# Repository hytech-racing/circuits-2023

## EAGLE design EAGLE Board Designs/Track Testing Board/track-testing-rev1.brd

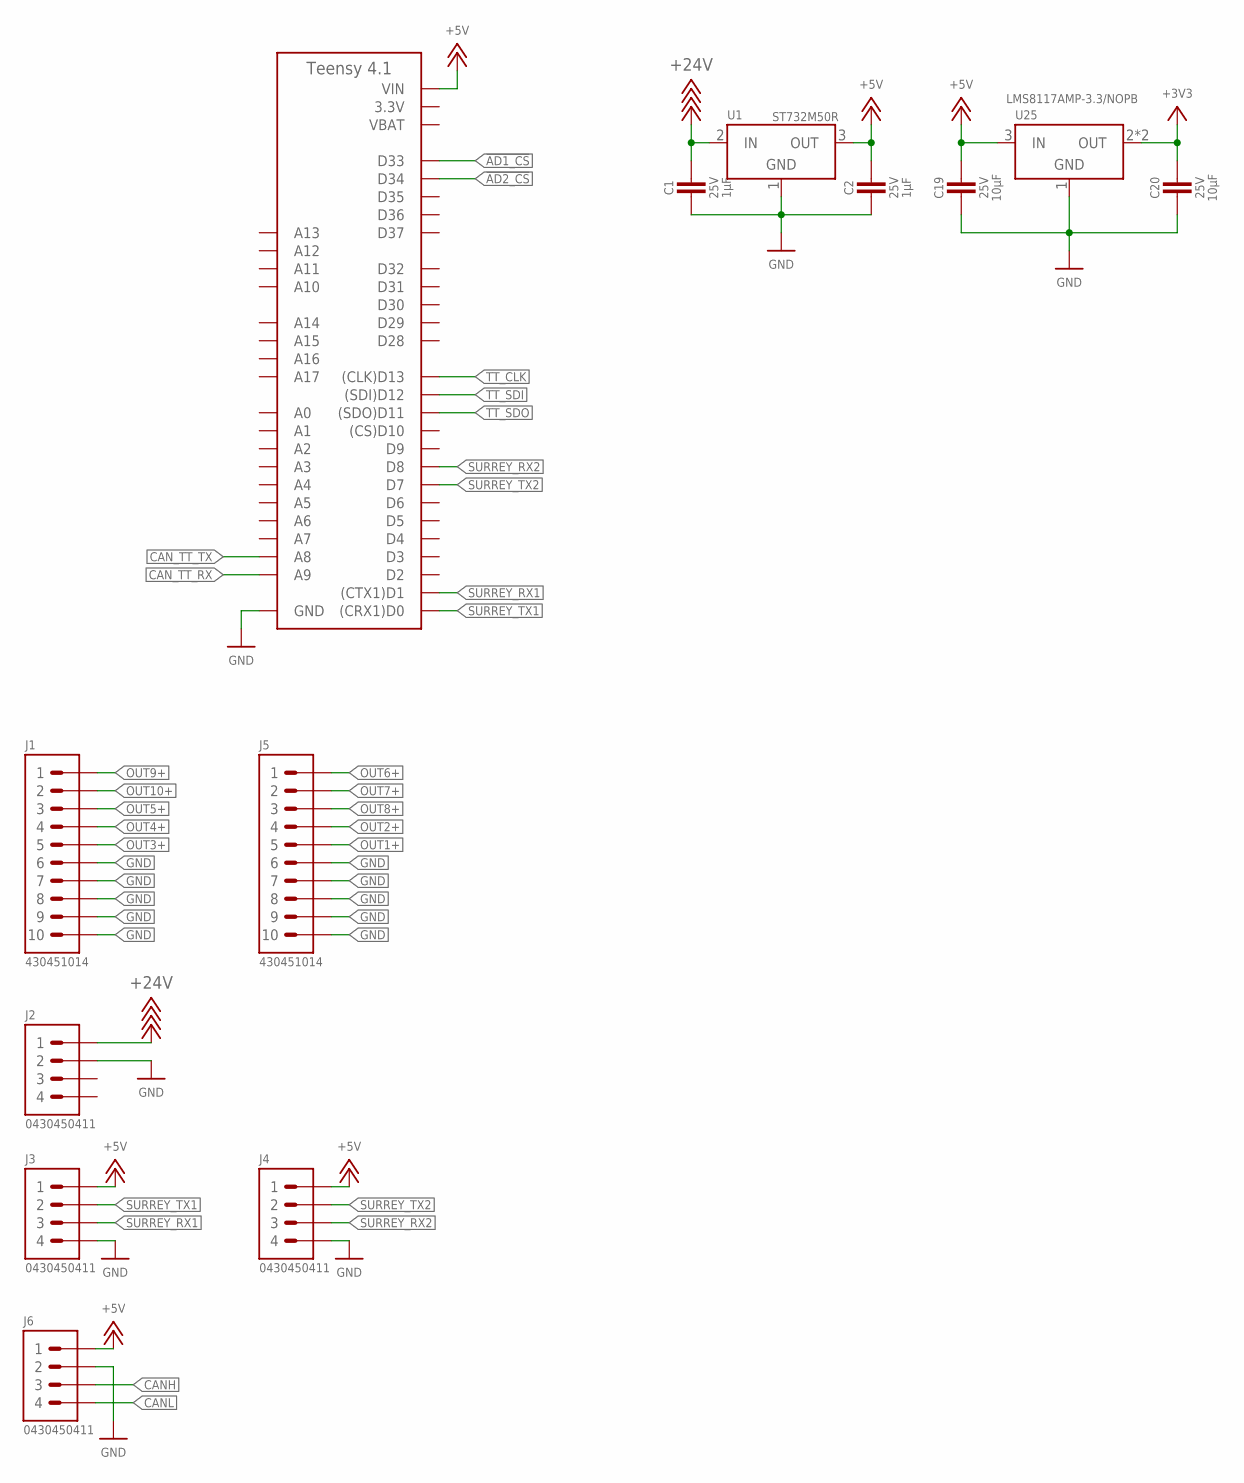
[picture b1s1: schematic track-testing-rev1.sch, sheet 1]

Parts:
A1: TEENSY_4.1; TEENSY_LONG_EXT
C1, C2: CAPACITOR_0603_25V_1UF; 0603-CAP
C19, C20: CAPACITOR_0603_25V_10UF; 0603-CAP
J1, J5: CONNECTOR-10_MF_T_V_; MOLEX_MICROFIT_PTH_VERTICAL_10_DUAL
J2, J3, J4, J6: CONNECTOR-4_μF_S_RA_; MOLEX_MICROFIT_SMD_RIGHTANGLE_04_DUAL
U1: VOLTAGE_REGULATOR_SOT-23-5_5V; SOT-23-5
U25: VOLTAGE_REGULATOR_SOT-223_3.3V; SOT-223

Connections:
3.3V: A1.3V3 (3.3V), A1.3V3@2 (3.3V), A1.3V3@3 (3.3V)
!AD1_CS: A1.D33; also elsewhere on the board
!AD2_CS: A1.D34; also elsewhere on the board
+3V3: C20.1, U25.2 (OUT), U25.4 (OUT); also elsewhere on the board
+5V: A1.VIN, C2.1, C19.1, J3.1, J4.1, J6.1, U1.3 (OUT), U25.3 (IN); also elsewhere on the board
+24V: C1.1, J2.1, U1.2 (IN)
CANH: J6.3; also elsewhere on the board
CANL: J6.4; also elsewhere on the board
CAN_TT_RX: A1.D23 (A9); also elsewhere on the board
CAN_TT_TX: A1.D22 (A8); also elsewhere on the board
GND: A1.AGND/GND (GND), A1.GND, A1.GND@2 (GND), C1.2, C2.2, C19.2, C20.2, J1.6, J1.7, J1.8, J1.9, J1.10, J2.2, J3.4, J4.4, J5.6, J5.7, J5.8, J5.9, J5.10, J6.2, U1.1 (GND), U25.1 (GND); also elsewhere on the board
OUT1+: J5.5; also elsewhere on the board
OUT2+: J5.4; also elsewhere on the board
OUT3+: J1.5; also elsewhere on the board
OUT4+: J1.4; also elsewhere on the board
OUT5+: J1.3; also elsewhere on the board
OUT6+: J5.1; also elsewhere on the board
OUT7+: J5.2; also elsewhere on the board
OUT8+: J5.3; also elsewhere on the board
OUT9+: J1.1; also elsewhere on the board
OUT10+: J1.2; also elsewhere on the board
SURREY_RX1: A1.D1 ((CTX1)D1), J3.3
SURREY_RX2: A1.D8, J4.3
SURREY_TX1: A1.D0 ((CRX1)D0), J3.2
SURREY_TX2: A1.D7, J4.2
TT_CLK: A1.D13 ((CLK)D13); also elsewhere on the board
TT_SDI: A1.D12 ((SDI)D12); also elsewhere on the board
TT_SDO: A1.D11 ((SDO)D11); also elsewhere on the board
VBAT: A1.VBAT

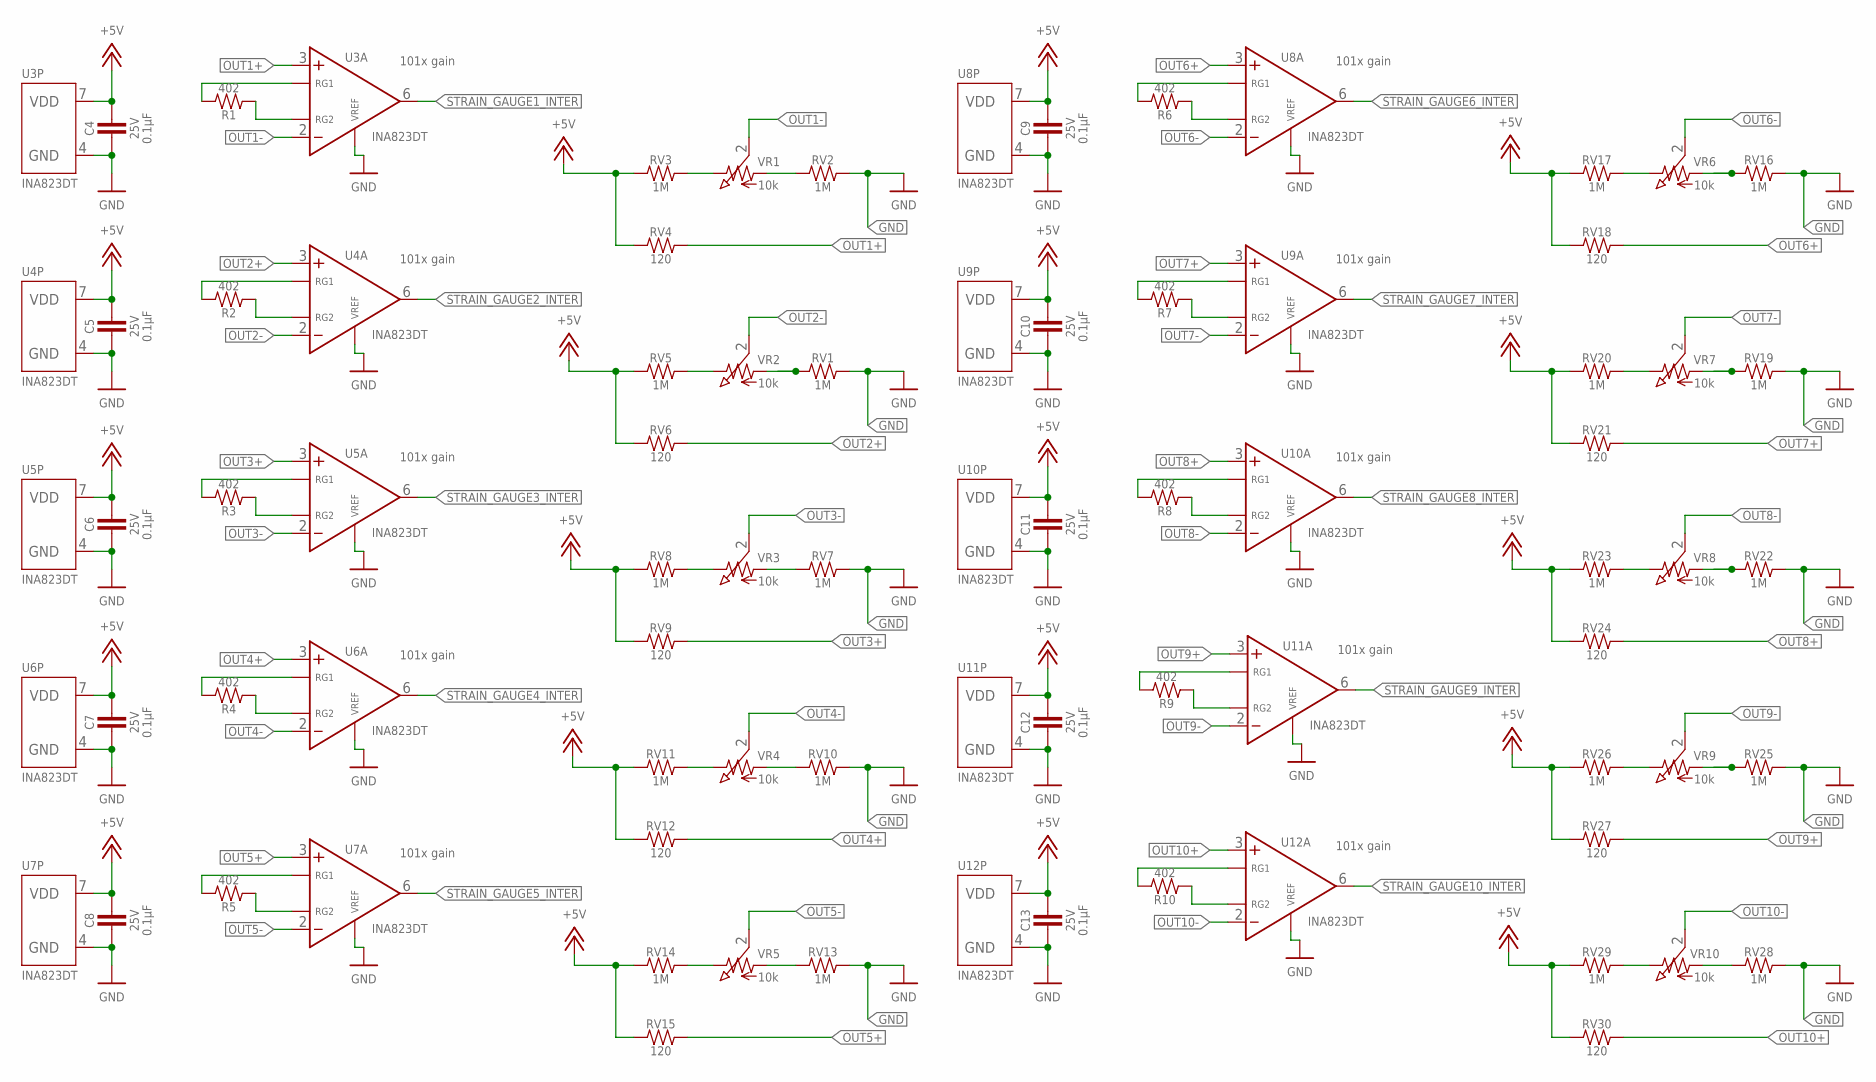
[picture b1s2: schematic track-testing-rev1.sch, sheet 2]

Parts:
C4, C5, C6, C7, C8, C9, C10, C11, C12, C13: CAPACITOR_0603_25V_0.1UF; 0603-CAP
R1, R2, R3, R4, R5, R6, R7, R8, R9, R10: RESISTOR_0603_402; 0603-RES
RV1, RV2, RV3, RV5, RV7, RV8, RV10, RV11, RV13, RV14, RV16, RV17, RV19, RV20, RV22, RV23, RV25, RV26, RV28, RV29: 1M; 0603-RES
RV4, RV6, RV9, RV12, RV15, RV18, RV21, RV24, RV27, RV30: 120; 0603-RES
U3, U4, U5, U6, U7, U8, U9, U10, U11, U12: INA823DT; SOIC-08(NARROW,0.15")
VR1, VR2, VR3, VR4, VR5, VR6, VR7, VR8, VR9, VR10: RESISTOR_TRIMPOT_10K_3362P; 3362P

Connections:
+5V: C4.1, C5.1, C6.1, C7.1, C8.1, C9.1, C10.1, C11.1, C12.1, C13.1, RV3.1, RV4.1, RV5.1, RV6.1, RV8.1, RV9.1, RV11.1, RV12.1, RV14.1, RV15.1, RV17.1, RV18.1, RV20.1, RV21.1, RV23.1, RV24.1, RV26.1, RV27.1, RV29.1, RV30.1, U3.7 (VDD), U4.7 (VDD), U5.7 (VDD), U6.7 (VDD), U7.7 (VDD), U8.7 (VDD), U9.7 (VDD), U10.7 (VDD), U11.7 (VDD), U12.7 (VDD); also elsewhere on the board
GND: C4.2, C5.2, C6.2, C7.2, C8.2, C9.2, C10.2, C11.2, C12.2, C13.2, RV1.2, RV2.2, RV7.2, RV10.2, RV13.2, RV16.2, RV19.2, RV22.2, RV25.2, RV28.2, U3.4 (GND), U3.5 (VREF), U4.4 (GND), U4.5 (VREF), U5.4 (GND), U5.5 (VREF), U6.4 (GND), U6.5 (VREF), U7.4 (GND), U7.5 (VREF), U8.4 (GND), U8.5 (VREF), U9.4 (GND), U9.5 (VREF), U10.4 (GND), U10.5 (VREF), U11.4 (GND), U11.5 (VREF), U12.4 (GND), U12.5 (VREF); also elsewhere on the board
unnamed: R2.2, U4.1 (RG1)
unnamed: R1.2, U3.1 (RG1)
unnamed: R1.1, U3.8 (RG2)
unnamed: R2.1, U4.8 (RG2)
unnamed: R3.2, U5.1 (RG1)
unnamed: R6.2, U8.1 (RG1)
unnamed: R3.1, U5.8 (RG2)
unnamed: R6.1, U8.8 (RG2)
unnamed: R4.2, U6.1 (RG1)
unnamed: R7.2, U9.1 (RG1)
unnamed: R4.1, U6.8 (RG2)
unnamed: R5.2, U7.1 (RG1)
unnamed: R5.1, U7.8 (RG2)
unnamed: R7.1, U9.8 (RG2)
unnamed: R8.2, U10.1 (RG1)
unnamed: R8.1, U10.8 (RG2)
unnamed: R9.2, U11.1 (RG1)
unnamed: R9.1, U11.8 (RG2)
unnamed: R10.2, U12.1 (RG1)
unnamed: R10.1, U12.8 (RG2)
unnamed: RV2.1, VR1.1
unnamed: RV3.2, VR1.3 (2)
unnamed: RV1.1, VR2.1
unnamed: RV5.2, VR2.3 (2)
unnamed: RV11.2, VR4.3 (2)
unnamed: RV7.1, VR3.1
unnamed: RV8.2, VR3.3 (2)
unnamed: RV10.1, VR4.1
unnamed: RV14.2, VR5.3 (2)
unnamed: RV13.1, VR5.1
unnamed: RV16.1, VR6.1
unnamed: RV17.2, VR6.3 (2)
unnamed: RV19.1, VR7.1
unnamed: RV20.2, VR7.3 (2)
unnamed: RV22.1, VR8.1
unnamed: RV23.2, VR8.3 (2)
unnamed: RV25.1, VR9.1
unnamed: RV26.2, VR9.3 (2)
unnamed: RV28.1, VR10.1
unnamed: RV29.2, VR10.3 (2)
OUT1+: RV4.2, U3.3 (VIN+); also elsewhere on the board
OUT1-: U3.2 (VIN-), VR1.2 (3)
OUT2+: RV6.2, U4.3 (VIN+); also elsewhere on the board
OUT2-: U4.2 (VIN-), VR2.2 (3)
OUT3+: RV9.2, U5.3 (VIN+); also elsewhere on the board
OUT3-: U5.2 (VIN-), VR3.2 (3)
OUT4+: RV12.2, U6.3 (VIN+); also elsewhere on the board
OUT4-: U6.2 (VIN-), VR4.2 (3)
OUT5+: RV15.2, U7.3 (VIN+); also elsewhere on the board
OUT5-: U7.2 (VIN-), VR5.2 (3)
OUT6+: RV18.2, U8.3 (VIN+); also elsewhere on the board
OUT6-: U8.2 (VIN-), VR6.2 (3)
OUT7+: RV21.2, U9.3 (VIN+); also elsewhere on the board
OUT7-: U9.2 (VIN-), VR7.2 (3)
OUT8+: RV24.2, U10.3 (VIN+); also elsewhere on the board
OUT8-: U10.2 (VIN-), VR8.2 (3)
OUT9+: RV27.2, U11.3 (VIN+); also elsewhere on the board
OUT9-: U11.2 (VIN-), VR9.2 (3)
OUT10+: RV30.2, U12.3 (VIN+); also elsewhere on the board
OUT10-: U12.2 (VIN-), VR10.2 (3)
STRAIN_GAUGE1_INTER: U3.6 (VOUT); also elsewhere on the board
STRAIN_GAUGE2_INTER: U4.6 (VOUT); also elsewhere on the board
STRAIN_GAUGE3_INTER: U5.6 (VOUT); also elsewhere on the board
STRAIN_GAUGE4_INTER: U6.6 (VOUT); also elsewhere on the board
STRAIN_GAUGE5_INTER: U7.6 (VOUT); also elsewhere on the board
STRAIN_GAUGE6_INTER: U8.6 (VOUT); also elsewhere on the board
STRAIN_GAUGE7_INTER: U9.6 (VOUT); also elsewhere on the board
STRAIN_GAUGE8_INTER: U10.6 (VOUT); also elsewhere on the board
STRAIN_GAUGE9_INTER: U11.6 (VOUT); also elsewhere on the board
STRAIN_GAUGE10_INTER: U12.6 (VOUT); also elsewhere on the board

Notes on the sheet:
101x gain

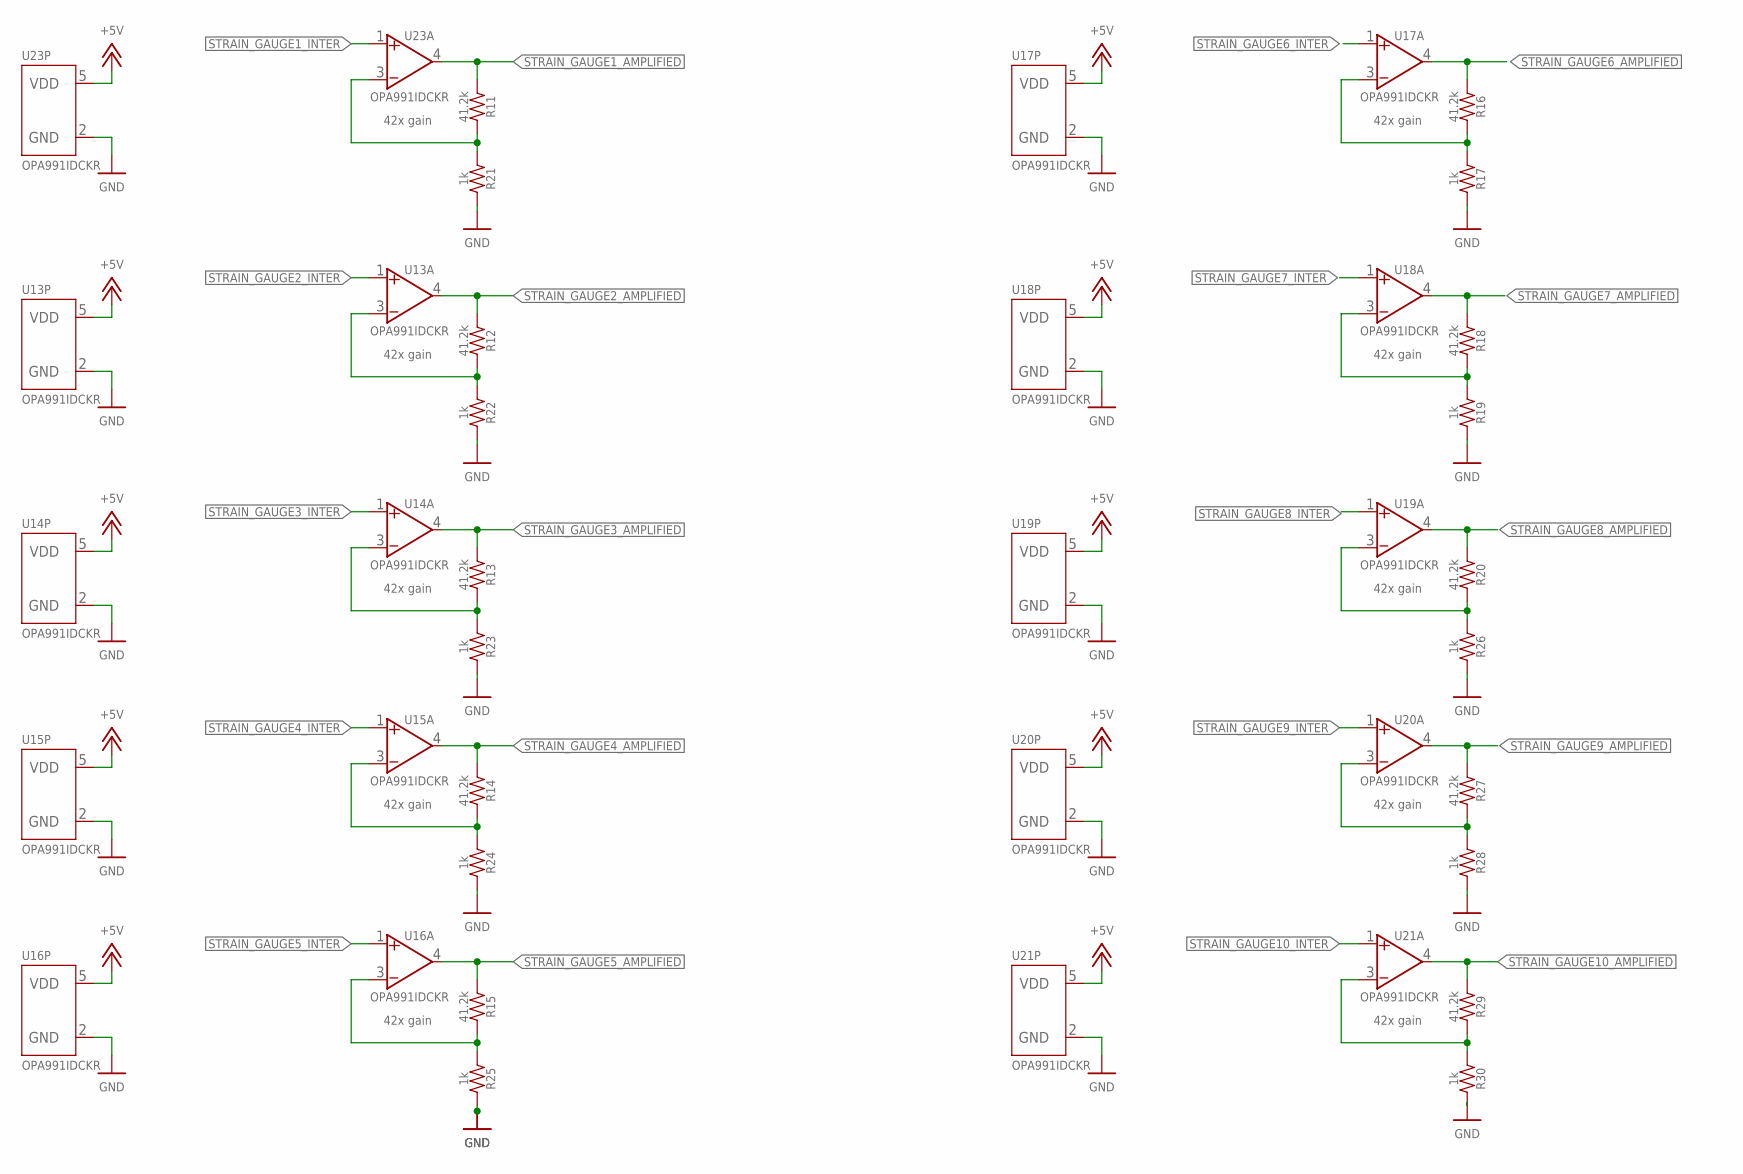
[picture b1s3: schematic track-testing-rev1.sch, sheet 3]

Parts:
R11, R12, R13, R14, R15, R16, R18, R20, R27, R29: RESISTOR_0603_41.2K; 0603-RES
R17, R19, R21, R22, R23, R24, R25, R26, R28, R30: RESISTOR_0603_1K; 0603-RES
U13, U14, U15, U16, U17, U18, U19, U20, U21, U23: OPAMP_1_CHANNEL_OPA991; SC-70-5

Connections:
+5V: U13.5 (VDD), U14.5 (VDD), U15.5 (VDD), U16.5 (VDD), U17.5 (VDD), U18.5 (VDD), U19.5 (VDD), U20.5 (VDD), U21.5 (VDD), U23.5 (VDD); also elsewhere on the board
GND: R17.2, R19.2, R21.2, R22.2, R23.2, R24.2, R25.2, R26.2, R28.2, R30.2, U13.2 (GND), U14.2 (GND), U15.2 (GND), U16.2 (GND), U17.2 (GND), U18.2 (GND), U19.2 (GND), U20.2 (GND), U21.2 (GND), U23.2 (GND); also elsewhere on the board
unnamed: R12.2, R22.1, U13.3 (VIN-)
unnamed: R11.2, R21.1, U23.3 (VIN-)
unnamed: R13.2, R23.1, U14.3 (VIN-)
unnamed: R14.2, R24.1, U15.3 (VIN-)
unnamed: R15.2, R25.1, U16.3 (VIN-)
unnamed: R16.2, R17.1, U17.3 (VIN-)
unnamed: R18.2, R19.1, U18.3 (VIN-)
unnamed: R20.2, R26.1, U19.3 (VIN-)
unnamed: R27.2, R28.1, U20.3 (VIN-)
unnamed: R29.2, R30.1, U21.3 (VIN-)
STRAIN_GAUGE1_AMPLIFIED: R11.1, U23.4 (VOUT); also elsewhere on the board
STRAIN_GAUGE1_INTER: U23.1 (VIN+); also elsewhere on the board
STRAIN_GAUGE2_AMPLIFIED: R12.1, U13.4 (VOUT); also elsewhere on the board
STRAIN_GAUGE2_INTER: U13.1 (VIN+); also elsewhere on the board
STRAIN_GAUGE3_AMPLIFIED: R13.1, U14.4 (VOUT); also elsewhere on the board
STRAIN_GAUGE3_INTER: U14.1 (VIN+); also elsewhere on the board
STRAIN_GAUGE4_AMPLIFIED: R14.1, U15.4 (VOUT); also elsewhere on the board
STRAIN_GAUGE4_INTER: U15.1 (VIN+); also elsewhere on the board
STRAIN_GAUGE5_AMPLIFIED: R15.1, U16.4 (VOUT); also elsewhere on the board
STRAIN_GAUGE5_INTER: U16.1 (VIN+); also elsewhere on the board
STRAIN_GAUGE6_AMPLIFIED: R16.1, U17.4 (VOUT); also elsewhere on the board
STRAIN_GAUGE6_INTER: U17.1 (VIN+); also elsewhere on the board
STRAIN_GAUGE7_AMPLIFIED: R18.1, U18.4 (VOUT); also elsewhere on the board
STRAIN_GAUGE7_INTER: U18.1 (VIN+); also elsewhere on the board
STRAIN_GAUGE8_AMPLIFIED: R20.1, U19.4 (VOUT); also elsewhere on the board
STRAIN_GAUGE8_INTER: U19.1 (VIN+); also elsewhere on the board
STRAIN_GAUGE9_AMPLIFIED: R27.1, U20.4 (VOUT); also elsewhere on the board
STRAIN_GAUGE9_INTER: U20.1 (VIN+); also elsewhere on the board
STRAIN_GAUGE10_AMPLIFIED: R29.1, U21.4 (VOUT); also elsewhere on the board
STRAIN_GAUGE10_INTER: U21.1 (VIN+); also elsewhere on the board

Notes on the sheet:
42x gain

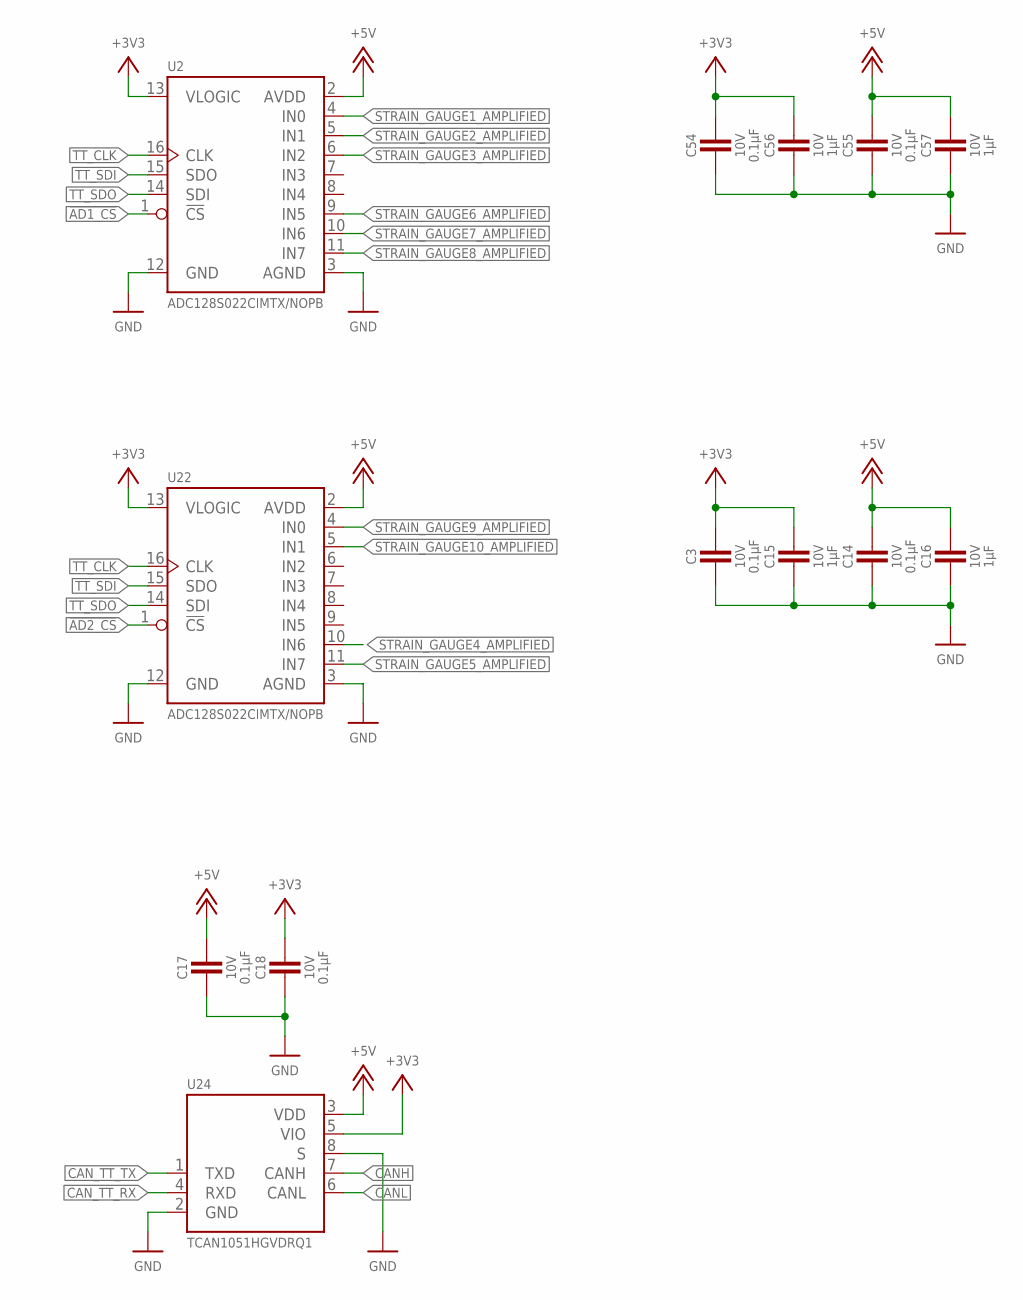
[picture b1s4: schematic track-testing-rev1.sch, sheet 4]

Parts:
C3, C14, C17, C18, C54, C55: CAPACITOR_0603_10V_0.1UF; 0603-CAP
C15, C16, C56, C57: CAPACITOR_0603_10V_1UF; 0603-CAP
U2, U22: ADC128S022; TSSOP-16
U24: TCAN1051HQV-Q1; SOIC-08(NARROW,0.15")

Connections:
!AD1_CS: U2.1 (!CS!); also elsewhere on the board
!AD2_CS: U22.1 (!CS!); also elsewhere on the board
+3V3: C3.1, C15.1, C18.1, C54.1, C56.1, U2.13 (VLOGIC), U22.13 (VLOGIC), U24.5 (VIO); also elsewhere on the board
+5V: C14.1, C16.1, C17.1, C55.1, C57.1, U2.2 (AVDD), U22.2 (AVDD), U24.3 (VDD); also elsewhere on the board
CANH: U24.7 (CANH); also elsewhere on the board
CANL: U24.6 (CANL); also elsewhere on the board
CAN_TT_RX: U24.4 (RXD); also elsewhere on the board
CAN_TT_TX: U24.1 (TXD); also elsewhere on the board
GND: C3.2, C14.2, C15.2, C16.2, C17.2, C18.2, C54.2, C55.2, C56.2, C57.2, U2.3 (AGND), U2.12 (GND), U22.3 (AGND), U22.12 (GND), U24.2 (GND), U24.8 (S); also elsewhere on the board
STRAIN_GAUGE1_AMPLIFIED: U2.4 (IN0); also elsewhere on the board
STRAIN_GAUGE2_AMPLIFIED: U2.5 (IN1); also elsewhere on the board
STRAIN_GAUGE3_AMPLIFIED: U2.6 (IN2); also elsewhere on the board
STRAIN_GAUGE4_AMPLIFIED: U22.10 (IN6); also elsewhere on the board
STRAIN_GAUGE5_AMPLIFIED: U22.11 (IN7); also elsewhere on the board
STRAIN_GAUGE6_AMPLIFIED: U2.9 (IN5); also elsewhere on the board
STRAIN_GAUGE7_AMPLIFIED: U2.10 (IN6); also elsewhere on the board
STRAIN_GAUGE8_AMPLIFIED: U2.11 (IN7); also elsewhere on the board
STRAIN_GAUGE9_AMPLIFIED: U22.4 (IN0); also elsewhere on the board
STRAIN_GAUGE10_AMPLIFIED: U22.5 (IN1); also elsewhere on the board
TT_CLK: U2.16 (CLK), U22.16 (CLK); also elsewhere on the board
TT_SDI: U2.15 (SDO), U22.15 (SDO); also elsewhere on the board
TT_SDO: U2.14 (SDI), U22.14 (SDI); also elsewhere on the board

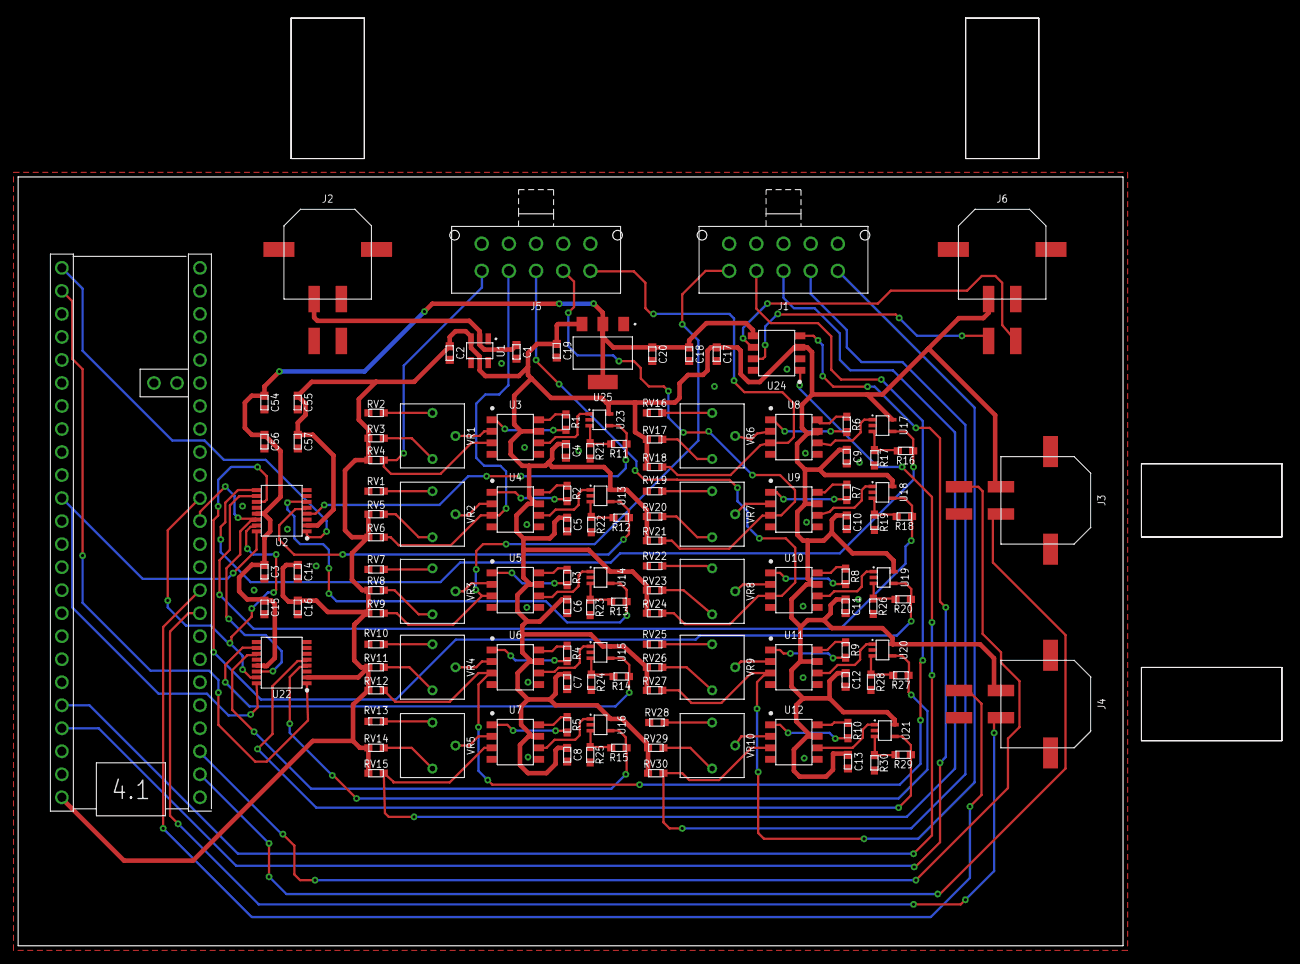
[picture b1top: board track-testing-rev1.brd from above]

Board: 2 copper layers, 139.4 x 102.4 mm, 126 parts (0 on the bottom side), 108 nets.

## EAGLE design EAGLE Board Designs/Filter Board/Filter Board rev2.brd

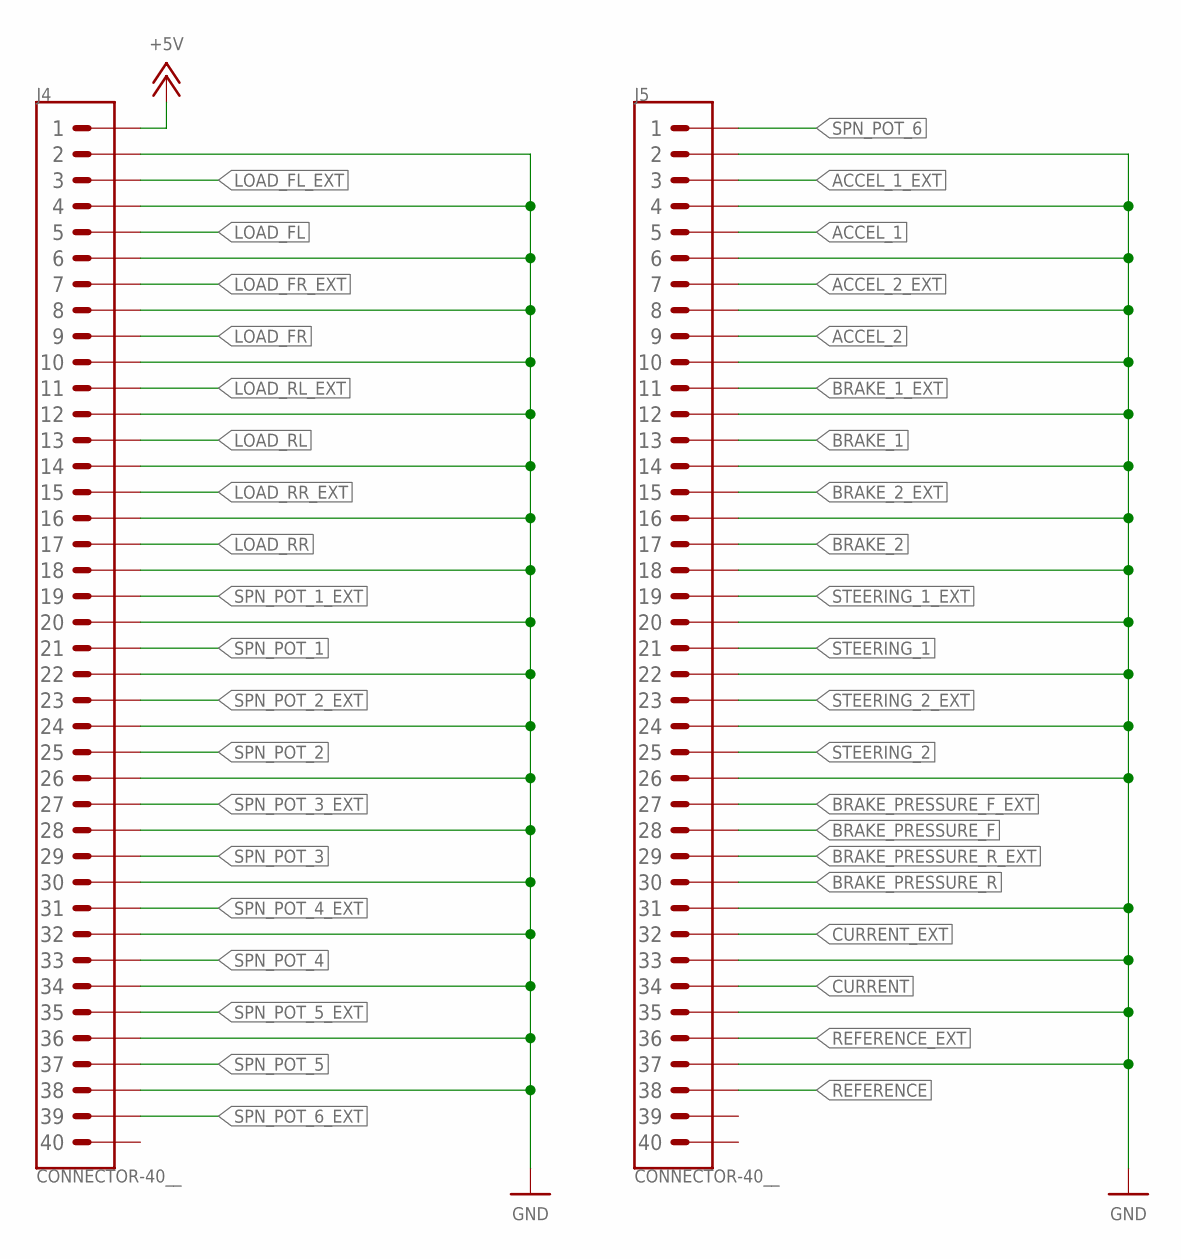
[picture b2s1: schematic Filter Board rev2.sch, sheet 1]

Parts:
J4, J5: CONNECTOR-40__; EHT-120-01

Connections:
+5V: J4.1; also elsewhere on the board
ACCEL_1: J5.5; also elsewhere on the board
ACCEL_1_EXT: J5.3; also elsewhere on the board
ACCEL_2: J5.9; also elsewhere on the board
ACCEL_2_EXT: J5.7; also elsewhere on the board
BRAKE_1: J5.13; also elsewhere on the board
BRAKE_1_EXT: J5.11; also elsewhere on the board
BRAKE_2: J5.17; also elsewhere on the board
BRAKE_2_EXT: J5.15; also elsewhere on the board
BRAKE_PRESSURE_F: J5.28; also elsewhere on the board
BRAKE_PRESSURE_F_EXT: J5.27; also elsewhere on the board
BRAKE_PRESSURE_R: J5.30; also elsewhere on the board
BRAKE_PRESSURE_R_EXT: J5.29; also elsewhere on the board
CURRENT: J5.34; also elsewhere on the board
CURRENT_EXT: J5.32; also elsewhere on the board
GND: J4.2, J4.4, J4.6, J4.8, J4.10, J4.12, J4.14, J4.16, J4.18, J4.20, J4.22, J4.24, J4.26, J4.28, J4.30, J4.32, J4.34, J4.36, J4.38, J5.2, J5.4, J5.6, J5.8, J5.10, J5.12, J5.14, J5.16, J5.18, J5.20, J5.22, J5.24, J5.26, J5.31, J5.33, J5.35, J5.37; also elsewhere on the board
LOAD_FL: J4.5; also elsewhere on the board
LOAD_FL_EXT: J4.3; also elsewhere on the board
LOAD_FR: J4.9; also elsewhere on the board
LOAD_FR_EXT: J4.7; also elsewhere on the board
LOAD_RL: J4.13; also elsewhere on the board
LOAD_RL_EXT: J4.11; also elsewhere on the board
LOAD_RR: J4.17; also elsewhere on the board
LOAD_RR_EXT: J4.15; also elsewhere on the board
REFERENCE: J5.38; also elsewhere on the board
REFERENCE_EXT: J5.36; also elsewhere on the board
SPN_POT_1: J4.21; also elsewhere on the board
SPN_POT_1_EXT: J4.19; also elsewhere on the board
SPN_POT_2: J4.25; also elsewhere on the board
SPN_POT_2_EXT: J4.23; also elsewhere on the board
SPN_POT_3: J4.29; also elsewhere on the board
SPN_POT_3_EXT: J4.27; also elsewhere on the board
SPN_POT_4: J4.33; also elsewhere on the board
SPN_POT_4_EXT: J4.31; also elsewhere on the board
SPN_POT_5: J4.37; also elsewhere on the board
SPN_POT_5_EXT: J4.35; also elsewhere on the board
SPN_POT_6: J5.1; also elsewhere on the board
SPN_POT_6_EXT: J4.39; also elsewhere on the board
STEERING_1: J5.21; also elsewhere on the board
STEERING_1_EXT: J5.19; also elsewhere on the board
STEERING_2: J5.25; also elsewhere on the board
STEERING_2_EXT: J5.23; also elsewhere on the board

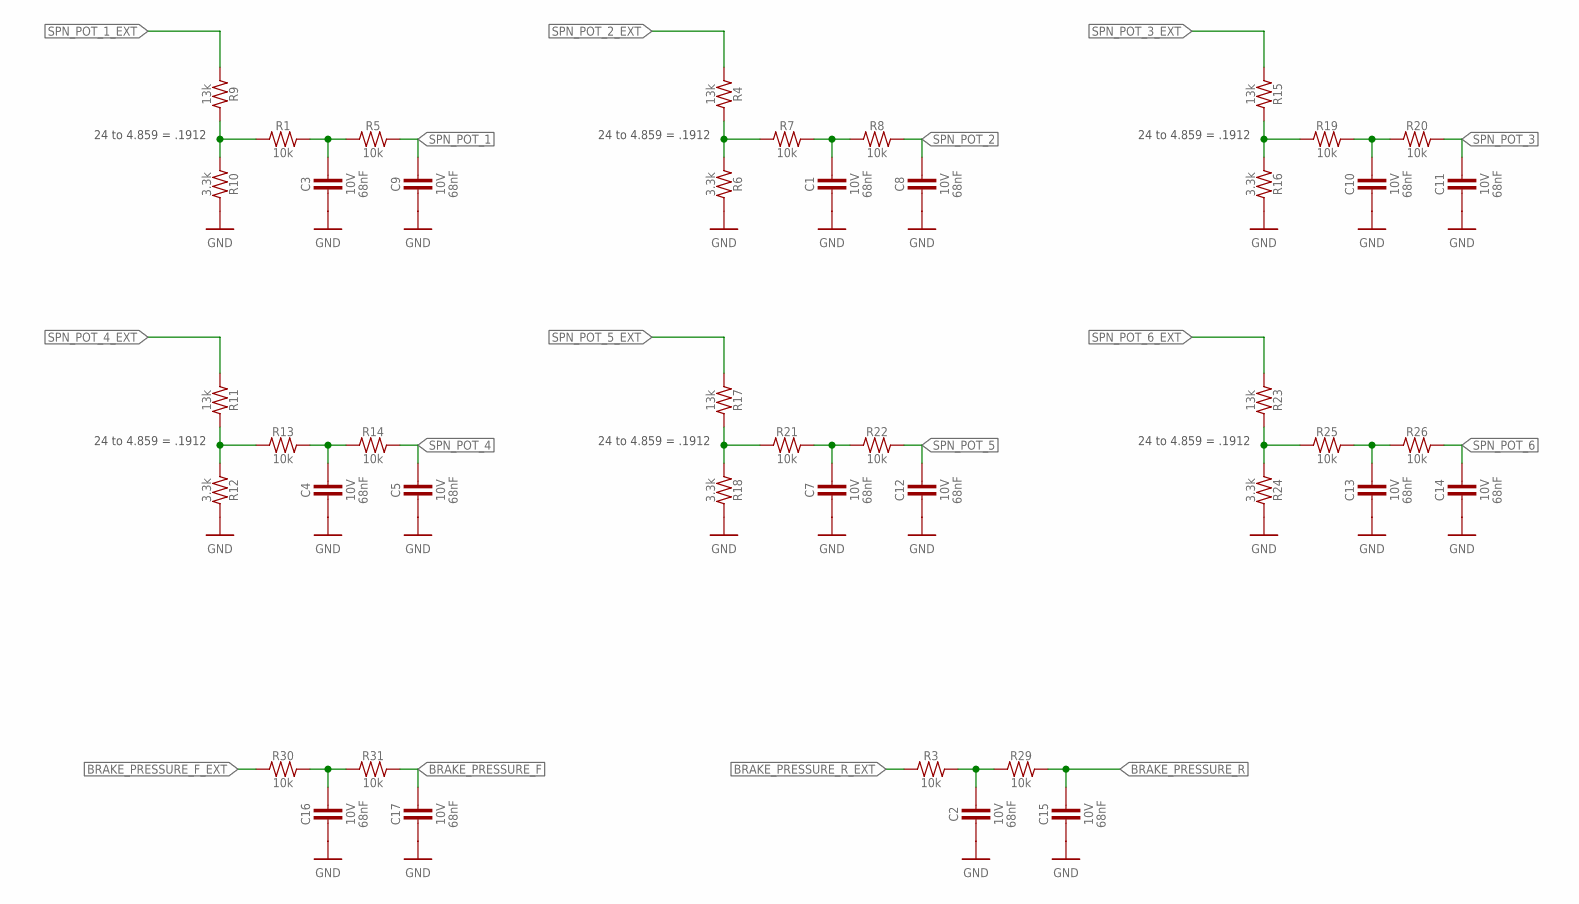
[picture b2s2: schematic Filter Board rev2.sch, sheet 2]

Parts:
C1, C2, C3, C4, C5, C7, C8, C9, C10, C11, C12, C13, C14, C15, C16, C17: CAPACITOR_0603_10V_68NF; 0603-CAP
R1, R3, R5, R7, R8, R13, R14, R19, R20, R21, R22, R25, R26, R29, R30, R31: RESISTOR_0603_10K; 0603-RES
R4, R9, R11, R15, R17, R23: RESISTOR_0603_13K; 0603-RES
R6, R10, R12, R16, R18, R24: RESISTOR_0603_3.3K; 0603-RES

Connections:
BRAKE_PRESSURE_F: C17.1, R31.2; also elsewhere on the board
BRAKE_PRESSURE_F_EXT: R30.1; also elsewhere on the board
BRAKE_PRESSURE_R: C15.1, R29.2; also elsewhere on the board
BRAKE_PRESSURE_R_EXT: R3.1; also elsewhere on the board
GND: C1.2, C2.2, C3.2, C4.2, C5.2, C7.2, C8.2, C9.2, C10.2, C11.2, C12.2, C13.2, C14.2, C15.2, C16.2, C17.2, R6.2, R10.2, R12.2, R16.2, R18.2, R24.2; also elsewhere on the board
unnamed: C3.1, R1.2, R5.1
unnamed: C1.1, R7.2, R8.1
unnamed: R1.1, R9.2, R10.1
unnamed: R4.2, R6.1, R7.1
unnamed: C10.1, R19.2, R20.1
unnamed: R15.2, R16.1, R19.1
unnamed: C4.1, R13.2, R14.1
unnamed: R11.2, R12.1, R13.1
unnamed: C7.1, R21.2, R22.1
unnamed: R17.2, R18.1, R21.1
unnamed: C13.1, R25.2, R26.1
unnamed: R23.2, R24.1, R25.1
unnamed: C2.1, R3.2, R29.1
unnamed: C16.1, R30.2, R31.1
SPN_POT_1: C9.1, R5.2; also elsewhere on the board
SPN_POT_1_EXT: R9.1; also elsewhere on the board
SPN_POT_2: C8.1, R8.2; also elsewhere on the board
SPN_POT_2_EXT: R4.1; also elsewhere on the board
SPN_POT_3: C11.1, R20.2; also elsewhere on the board
SPN_POT_3_EXT: R15.1; also elsewhere on the board
SPN_POT_4: C5.1, R14.2; also elsewhere on the board
SPN_POT_4_EXT: R11.1; also elsewhere on the board
SPN_POT_5: C12.1, R22.2; also elsewhere on the board
SPN_POT_5_EXT: R17.1; also elsewhere on the board
SPN_POT_6: C14.1, R26.2; also elsewhere on the board
SPN_POT_6_EXT: R23.1; also elsewhere on the board

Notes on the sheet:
24 to 4.859 = .1912

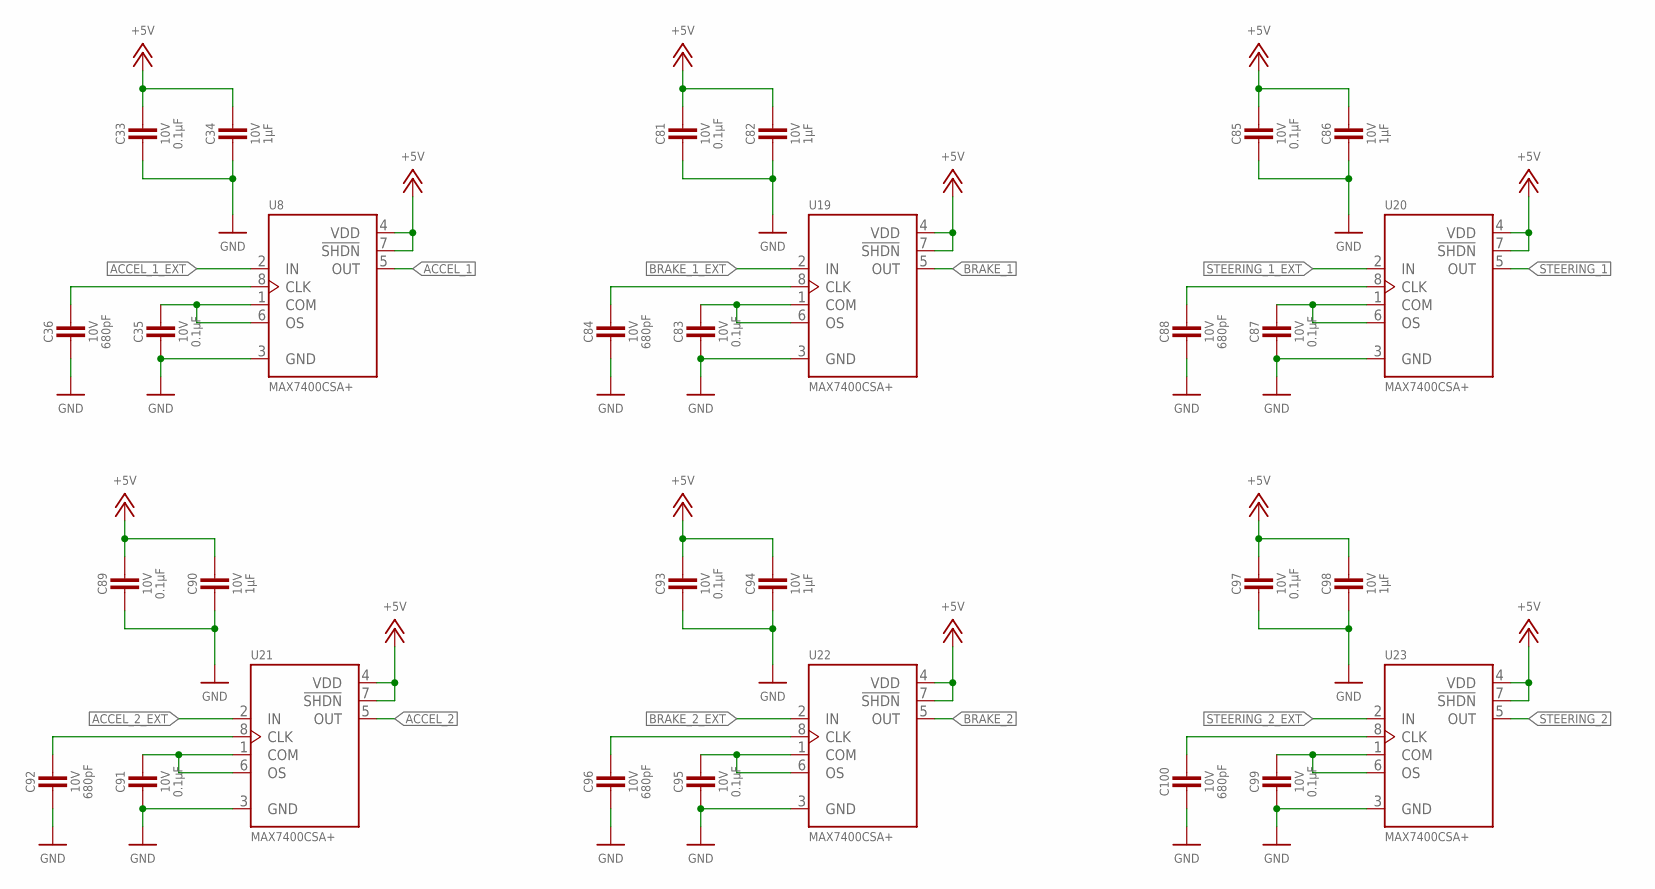
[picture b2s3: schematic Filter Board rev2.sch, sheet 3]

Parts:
C33, C35, C81, C83, C85, C87, C89, C91, C93, C95, C97, C99: CAPACITOR_0603_10V_0.1UF; 0603-CAP
C34, C82, C86, C90, C94, C98: CAPACITOR_0603_10V_1UF; 0603-CAP
C36, C84, C88, C92, C96, C100: CAPACITOR_0603_10V_680PF; 0603-CAP
U8, U19, U20, U21, U22, U23: MAX7400; SOIC-08(NARROW,0.15")

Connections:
+5V: C33.1, C34.1, C81.1, C82.1, C85.1, C86.1, C89.1, C90.1, C93.1, C94.1, C97.1, C98.1, U8.4 (VDD), U8.7 (!SHDN), U19.4 (VDD), U19.7 (!SHDN), U20.4 (VDD), U20.7 (!SHDN), U21.4 (VDD), U21.7 (!SHDN), U22.4 (VDD), U22.7 (!SHDN), U23.4 (VDD), U23.7 (!SHDN); also elsewhere on the board
ACCEL_1: U8.5 (OUT); also elsewhere on the board
ACCEL_1_EXT: U8.2 (IN); also elsewhere on the board
ACCEL_2: U21.5 (OUT); also elsewhere on the board
ACCEL_2_EXT: U21.2 (IN); also elsewhere on the board
BRAKE_1: U19.5 (OUT); also elsewhere on the board
BRAKE_1_EXT: U19.2 (IN); also elsewhere on the board
BRAKE_2: U22.5 (OUT); also elsewhere on the board
BRAKE_2_EXT: U22.2 (IN); also elsewhere on the board
GND: C33.2, C34.2, C35.2, C36.2, C81.2, C82.2, C83.2, C84.2, C85.2, C86.2, C87.2, C88.2, C89.2, C90.2, C91.2, C92.2, C93.2, C94.2, C95.2, C96.2, C97.2, C98.2, C99.2, C100.2, U8.3 (GND), U19.3 (GND), U20.3 (GND), U21.3 (GND), U22.3 (GND), U23.3 (GND); also elsewhere on the board
unnamed: C36.1, U8.8 (CLK)
unnamed: C35.1, U8.1 (COM), U8.6 (OS)
unnamed: C84.1, U19.8 (CLK)
unnamed: C83.1, U19.1 (COM), U19.6 (OS)
unnamed: C88.1, U20.8 (CLK)
unnamed: C87.1, U20.1 (COM), U20.6 (OS)
unnamed: C92.1, U21.8 (CLK)
unnamed: C91.1, U21.1 (COM), U21.6 (OS)
unnamed: C96.1, U22.8 (CLK)
unnamed: C95.1, U22.1 (COM), U22.6 (OS)
unnamed: C100.1, U23.8 (CLK)
unnamed: C99.1, U23.1 (COM), U23.6 (OS)
STEERING_1: U20.5 (OUT); also elsewhere on the board
STEERING_1_EXT: U20.2 (IN); also elsewhere on the board
STEERING_2: U23.5 (OUT); also elsewhere on the board
STEERING_2_EXT: U23.2 (IN); also elsewhere on the board
